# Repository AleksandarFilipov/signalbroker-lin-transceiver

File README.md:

# LIN

More images here: [link](doc/Pictures/)

## Installation 

### Prerequisites

Download USB drivers for the ESP device, choose driver depending on OS here:
https://www.olimex.com/Products/IoT/ESP32/ESP32-POE/open-source-hardware 

To be able to upload this project to your device you need PlatformIO. 
You can either install it as a [CLI application](https://docs.platformio.org/en/latest/core/index.html#) but the preferred way is to use their extension within an [IDE](https://docs.platformio.org/en/latest/integration/ide/pioide.html#).

I guess that the most popular is to use VS Code so I will use it in the example below.

#### VS Code

* [VS Code](https://code.visualstudio.com/)
* [PlatformIO Extension](https://marketplace.visualstudio.com/items?itemName=platformio.platformio-ide)

If you have installed the applications above, open this folder with VS Code.  

## Configuration

Configure the main.cpp file before uploading to the ESP32. 
### RibID - device identifier

The `rotary switch` is used to specify device identifier within the range 0..15. If you need need an id outside of the range you need to modify the source code.

>Alternatively you can hardcode, There is a `define` in the main.cpp file that holds the rib_id value for the ESP32. 

>If you have multiple ESP32 that should be connected to the same Beamy Broker, every ESP32 must have a unique rib_id.

### Master/Slave

`Master/Slave` is automatically set according to the proviced setting in `interfaces.json`

>On older PCB you need to set a jumper manually.

### DHCP

If you are intended to use DHCP the ethClient connect function should look like this
```cpp
ethClient.connect(config);
```

But if you are intended to use static IP, then the connect function should look like this instead
```cpp
ethClient.connect(config, false, IPAddress(192, 168, 1, 20), IPAddress(192, 168, 1, 10), IPAddress(255, 255, 255, 0));
```

So what does this mean? 

The false flag indicates that DHCP is disabled. 

The first IPAddress is the ESP32 address.

The second IPAdress is the host address (where the beamy broker is running)

The third IPAdress is a subnet address.

Now you are ready to upload this to your device!!

### Modify the interface.json on the server-side

When you have uploaded the firmware to your ESP32-devices and assigned them with unique rib IDs. You need to configure the interfaces.json file on the beamy broker-server side in the following way:

* namespace - Unique namespace name (you will access all necessary data from gRPC API with namespace name)
* device_identifier - rib ID that you assigned to the device
* target_host - null if using dhcp, otherwise type in IP address of esp32.
* server/target port - needs to be a unique port for each device
* node_mode: master/slave depending on how the device is connected to the LIN bus
* ldf_file - paste the link to where you have the LDF file
* schedule_file - same as ldf_file (like 99% of the times)
* schedule_table_name - type in which scheduler you want to use when you are running the device as the master
* schedule_autostart - if you are running as master and you want the provided schedule_table to autostart, this value should be true otherwise false

## Slave
If you are intended to run as a slave, your interface file should look like this (but with your settings and .ldf files). 

#### **Remember to set the right rib_id**

### DHCP

```json 
{
      "namespace": "lin_slave",
      "type": "lin",
      "config": {
        "device_identifier": 1,
        "server_port": 2014,
        "target_port": 2013
      },
      "node_mode": "slave",
      "ldf_file": "configuration/ldf_files/linone.ldf",
}
```

### Static IP

```json 
{
      "namespace": "lin_slave",
      "type": "lin",
      "config": {
        "device_identifier": 1,
        "server_port": 2014,
        "target_host": "192.168.0.20",
        "target_port": 2013
      },
      "node_mode": "slave",
      "ldf_file": "configuration/ldf_files/linone.ldf",
}
```

## Master

If you are intended to run as a master, your interface file should look like this.

### DHCP

```json 
{
      "namespace": "lin_master",
      "type": "lin",
      "config": {
        "device_identifier": 1,
        "server_port": 2014,
        "target_port": 2013
      },
      "node_mode": "master",
      "ldf_file": "configuration/ldf_files/linone.ldf",
      "schedule_file": "configuration/ldf_files/linone.ldf",
      "schedule_table_name": "linoneSchedule",
      "schedule_autostart": true
}
```

### Static IP

```json 
{
      "namespace": "lin_master",
      "type": "lin",
      "config": {
        "device_identifier": 1,
        "server_port": 2014,
        "target_host": "192.168.1.20",
        "target_port": 2013
      },
      "node_mode": "master",
      "ldf_file": "configuration/ldf_files/linone.ldf",
      "schedule_file": "configuration/ldf_files/linone.ldf",
      "schedule_table_name": "linoneSchedule",
      "schedule_autostart": true
}
```

### Debug

Logging is by default output to serial 
```
constexpr bool LOG_TO_SERIAL = true;
```
To print logs in beamy broker debug window
```
constexpr bool LOG_TO_SERIAL = false;
```

### PCB and 3D printable boxes

All ordering information of the RemotiveLIN V1.1 box along with a BOM can be found [here](/doc/Ordering%20Information)

The Box casing can be 3D printed from the [STL files](/doc/Ordering%20Information/STL%20Casing)

The PCB can be manufactured and most parts can be assempled on the PCB by www.jlcpcb.com by uploading the [gerber, BOM and pick and place files](/doc/Ordering%20Information/PCB%20V1.1%20JLCPCB%20Ordering). The parts that are not in stock at JLCPCB needs to be ordered from a seperate supplier and then handsoldered to the PCB. These part can be found in the [BOM Excel file](/doc/Ordering%20Information/Full%20BOM%20V1.1.xlsx).

#### Pinout dsub9

- 3 GND
- 7 Signal

#### Nice to know
The device does implement ping, which is helpful for debugging

>Intention is that the software supports older revision of the PCB, if that's not the case please let us know.

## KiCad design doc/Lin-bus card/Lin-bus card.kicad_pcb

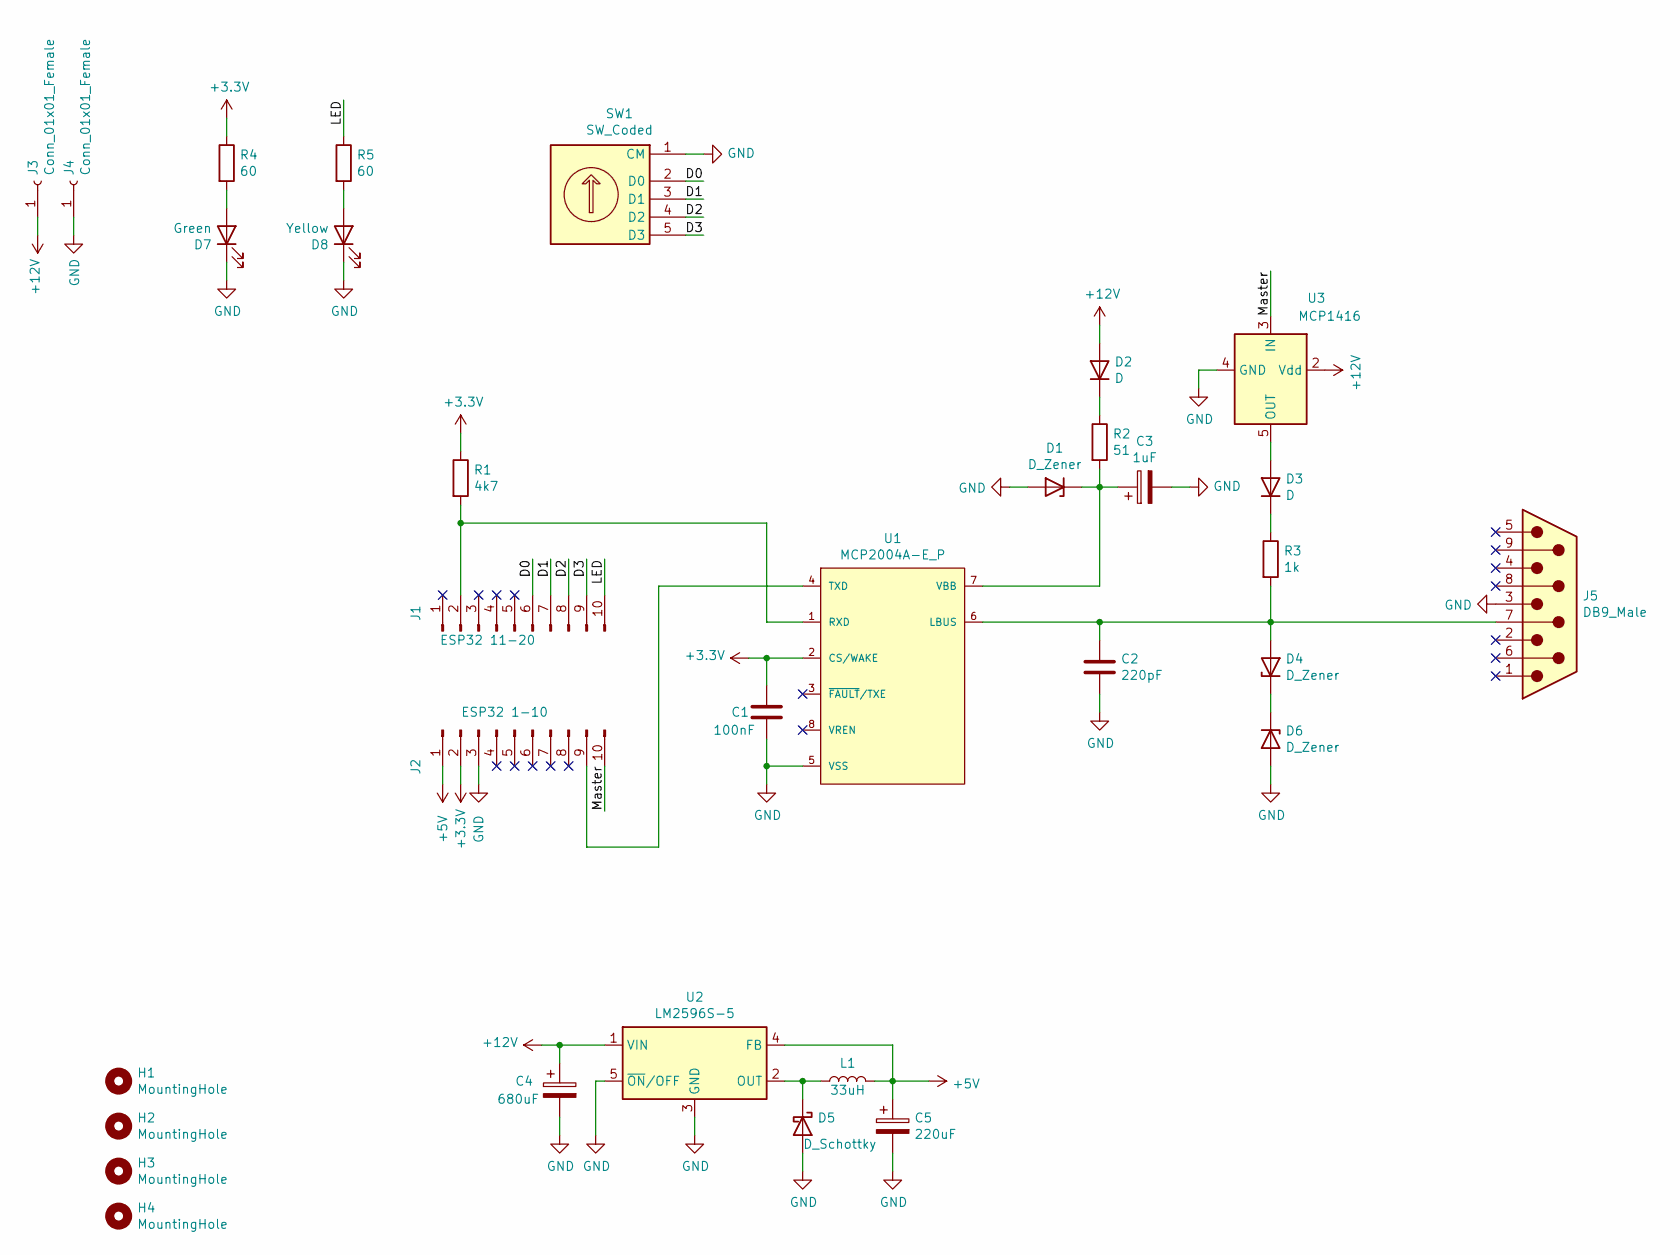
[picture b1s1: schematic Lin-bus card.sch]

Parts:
C1: 100nF; C_0603_1608Metric; LCSC C14663
C2: 220pF; C_0603_1608Metric; LCSC C1603
C3: 1uF; C_1206_3216Metric; LCSC C141744
C4: 680uF; 12.5x13.5cp-AS; LCSC C98216
C5: 220uF; CP_Elec_6.3x7.7; LCSC C2887273
D1: D_Zener; D_SOD-123F; LCSC C485499
D2, D3: D; D_SMA; LCSC C727081
D4, D6: D_Zener; D_SOD-323; LCSC C22621
D5: D_Schottky; D_SMA; LCSC C22452
D7: Green; Small_LED
D8: Yellow; Small_LED
H1, H2, H3, H4: MountingHole; MountingHole_3.2mm_M3
J1: ESP32 11-20; PinHeader_1x10_P2.54mm_Vertical; LCSC C2894933
J2: ESP32 1-10; PinHeader_1x10_P2.54mm_Vertical; LCSC C2894933
J3, J4: Conn_01x01_Female; Banana_Jack
J5: DB9_Male; DSUB-9_Male_Horizontal_P2.77x2.84mm_EdgePinOffset7.70mm_Hou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; LCSC C75750
L1: 33uH; L_Wuerth_HCI-5040; LCSC C83451
R1: 4k7; R_0603_1608Metric; LCSC C269694
R2: 51; R_0603_1608Metric; LCSC C23197
R3: 1k; R_0603_1608Metric; LCSC C14676
R4, R5: 60; R_0603_1608Metric
SW1: SW_Coded; Rotary_Encoder_AS
U1: MCP2004A-E_P; DIP-8_W7.62mm_Socket; LCSC C72124
U2: LM2596S-5; TO-263-5_TabPin3; LCSC C347421
U3: MCP1416; SOT-23-5

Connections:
+3V3: C1.1, J2.2, R1.1, R4.1, U1.2 (CS/WAKE)
+5V: C5.1, J2.1, L1.2, U2.4 (FB)
+12V: C4.1, D2.2 (A), J3.1, U2.1 (VIN), U3.2 (Vdd)
/D0: J1.6, SW1.2 (D0)
/D1: J1.7, SW1.3 (D1)
/D2: J1.8, SW1.4 (D2)
/D3: J1.9, SW1.5 (D3)
/LED: J1.10, R5.1
/Master: J2.10, U3.3 (IN)
GND: C1.2, C2.2, C3.2, C4.2, C5.2, D1.2 (A), D5.2 (A), D6.2 (A), D7.1 (K), D8.1 (K), J2.3, J4.1, J5.3, SW1.1 (CM), U1.5 (VSS), U2.3 (GND), U2.5 (~ON~/OFF), U3.4 (GND)
unnamed: C2.1, D4.2 (A), J5.7, R3.2, U1.6 (LBUS)
unnamed: C3.1, D1.1 (K), R2.2, U1.7 (VBB)
unnamed: D2.1 (K), R2.1
unnamed: D3.1 (K), R3.1
unnamed: D3.2 (A), U3.5 (OUT)
unnamed: D4.1 (K), D6.1 (K)
unnamed: D5.1 (K), L1.1, U2.2 (OUT)
unnamed: D7.2 (A), R4.2
unnamed: D8.2 (A), R5.2
unnamed: J1.2, R1.2, U1.1 (RXD)
unnamed: J2.9, U1.4 (TXD)

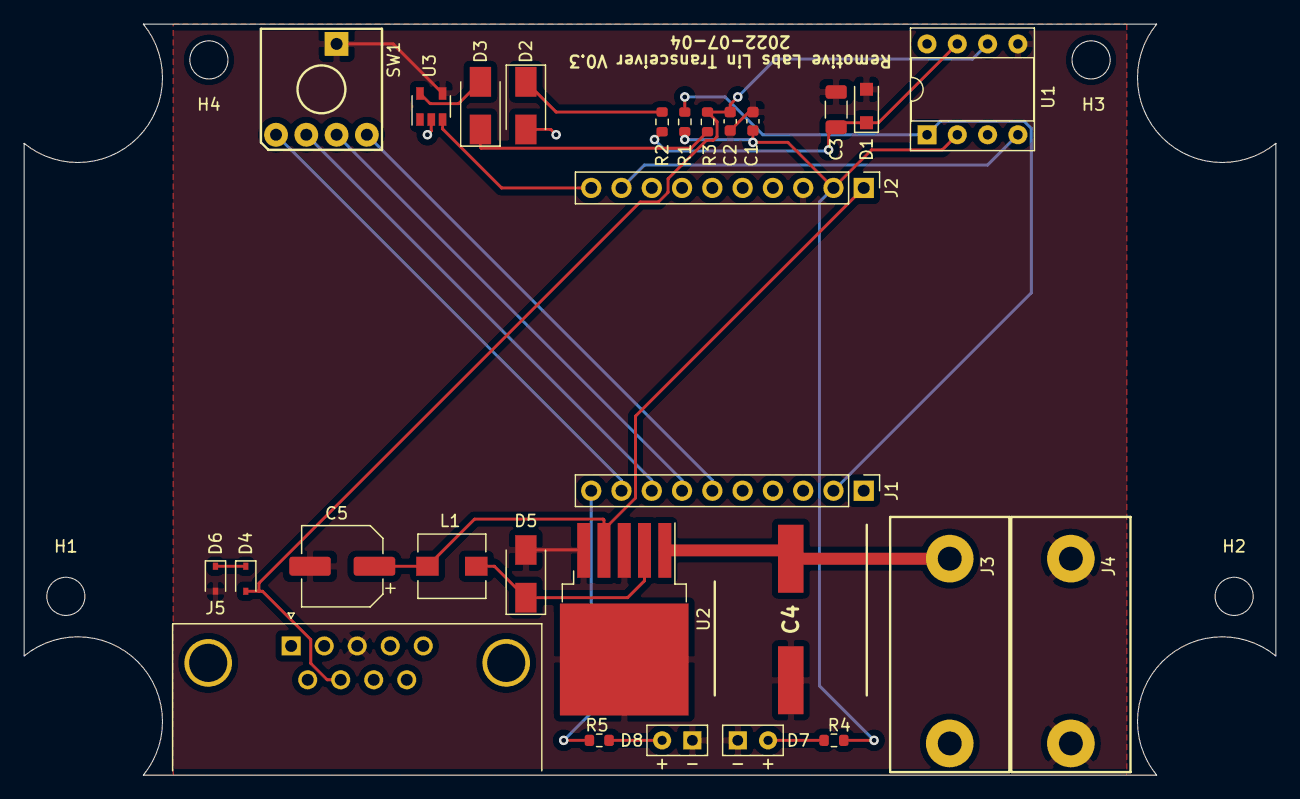
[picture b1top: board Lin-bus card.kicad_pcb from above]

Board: 2 copper layers, 105.0 x 63.0 mm, 32 parts (0 on the bottom side), 21 nets.

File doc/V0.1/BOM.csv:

Comment,Designator,Footprint,LCSC Part Number
100nF,C1,0603,C14663
220pF,C2,0603,C1603
1uF,C3,CASE-A_3216,C141744
680uF,C4,12.5x13.5mm,C98216
220uF,C5,6.3x7.7mm,C2887273
Zener,D1,SOD-123F,C485499
General purpose,"D2,D3",DO-214AC,C727081
Zener,"D4,D6",SOD-323,C22621
Schottky,D5,DO-214AC,C22452
33uH,L1,6.0x6.0mm,C83451
4K7,R1,0603,C269694
51R,R2,0603,C23197
1K,R3,0603,C14676
Socket,U1,DIP-8,C72124
DC-DC Regulator,U2,TO-263,C347421
Pin Header,"J1,J2",HDR-TH,C2894933
D-Sub,J5,DB9-TH,C75750

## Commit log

2021-01-25 bump header since protocol changed
2021-07-16 make sure slave runs regardless if there is a present operational master
2021-09-21 init lintransceiver with rp
2021-09-21 fetch config data OK
2021-09-21 moved code to config
2021-09-23 flashed on rig, thursday 23 sept
2021-10-04 added records file
2021-10-04 added code to test one lin
2021-10-04 added config settings
2021-10-04 added broadcast for config
2021-10-04 increment udp rx counter
2021-10-04 added run_slave fn
2021-10-04 added serial to struct
2021-10-04 removed unused things
2021-10-04 updated gitignore
2021-10-04 added serial-port to Cargo
2021-10-04 bugfix, before it tried to access index from an array that never existed
2021-10-04 added lin-bus, tracing crates
2021-10-04 Changed NodeMode to be enum instead of u8
2021-10-04 Finished with Master running, works ok with arbitration, still some problem with masterframe
2021-10-04 changed the functions for record a little bit
2021-10-07 slave with some bugs
2021-10-07 updated Cargo
2021-10-11 added README
2021-10-11 added authors
2021-10-11 added configuration-parser from file
2021-10-11 added default lin_config as example
2021-10-11 updated .gitignore
2021-10-11 updated Cargo.toml
2021-10-11 added lib.rs
2021-10-11 moved out variables to lib.rs
2021-10-11 try to optimize the lin_client
2021-10-11 removed Cargo.lock
2021-10-11 added config in readme
2021-10-14 added assets
2021-10-15 trying to find a solution for timing problem
2021-10-18 config and lin_udp_client runs in the same thread now
2021-10-18 added cargo configuration for compile with raspberry toolchain
2021-10-18 now, the script will take one argument, that is the ip of the pi
2021-10-18 changed heart_beat_period to a duration instead of being a u64
2021-10-18 moved the init of udp listen/sender to the init function instead of being in the run
2021-10-18 deleted an unnecessary scope
2021-10-18 nicer syntax when using udp_sender
2021-10-18 import debug macro
2021-10-18 handle errors i function
2021-10-18 remove check if udp message was intended for this id, since we are already handle this in the main file
2021-10-18 added comment
2021-10-18 added lin_bus PID and std error
2021-10-18 From now, the new function returning a result instead, so we can do handle error on serialbus
2021-10-18 error handling
2021-10-18 handle errors
2021-10-18 idea stuffs
2021-10-18 <add watchdog
2021-10-18 added linker for raspberry
2021-10-18 added buildsteps in readme
2021-10-18 changed the deploy to build a release binary
2021-10-18 Create esp32-build.yml
    Add CI for push and PR's.
2021-10-18 added github action
2021-10-18 added test in github action
2021-10-18 added some standard tests
2021-10-18 try to remove test in github actions
2021-10-18 pass target as argument instead, so we can run test in github actions
2021-11-26 master working
2021-11-26 fix master freeze
2021-12-08 added build dir
2021-12-08 fix so the flag useDHCP actutally does what it says
2021-12-08 fixed typos
2021-12-26 Update README.md
    Fix static ip, should be defined as string.
2022-07-25 set id using rotation dial
2022-07-25 automatically set master-slave
2022-07-26 use led to flash when traffic arrives or is sent
2022-07-26 added antons updated pcb
2022-07-26 added STLs for casing
2022-08-17 added images, updated readme
2022-08-17 fixed value on resistor
2022-08-17 allow manual rib id selection in order to stay compaible with older pcb:s
2022-08-17 mini fix readme
2022-10-09 RemotiveLIN V1.1 with new reverse polarity protection mosfet. Updated README file with new ordering information for the box. Updated dimensions in the STL file for 3D printing of the box.
2022-11-18 Ordering information of the PCB and casing added to README
2022-11-18 Typos in README fixed
2022-12-05 Reduce time from id to data for master, now removed 5ms between id and payload
2024-08-28 Re-flush if flush failed.
2024-09-02 add ability to change configuration port device -> server
2025-05-07 Update README.md, add pinout info
